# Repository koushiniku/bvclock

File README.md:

# bvclock
A wall clock on a breadboard.

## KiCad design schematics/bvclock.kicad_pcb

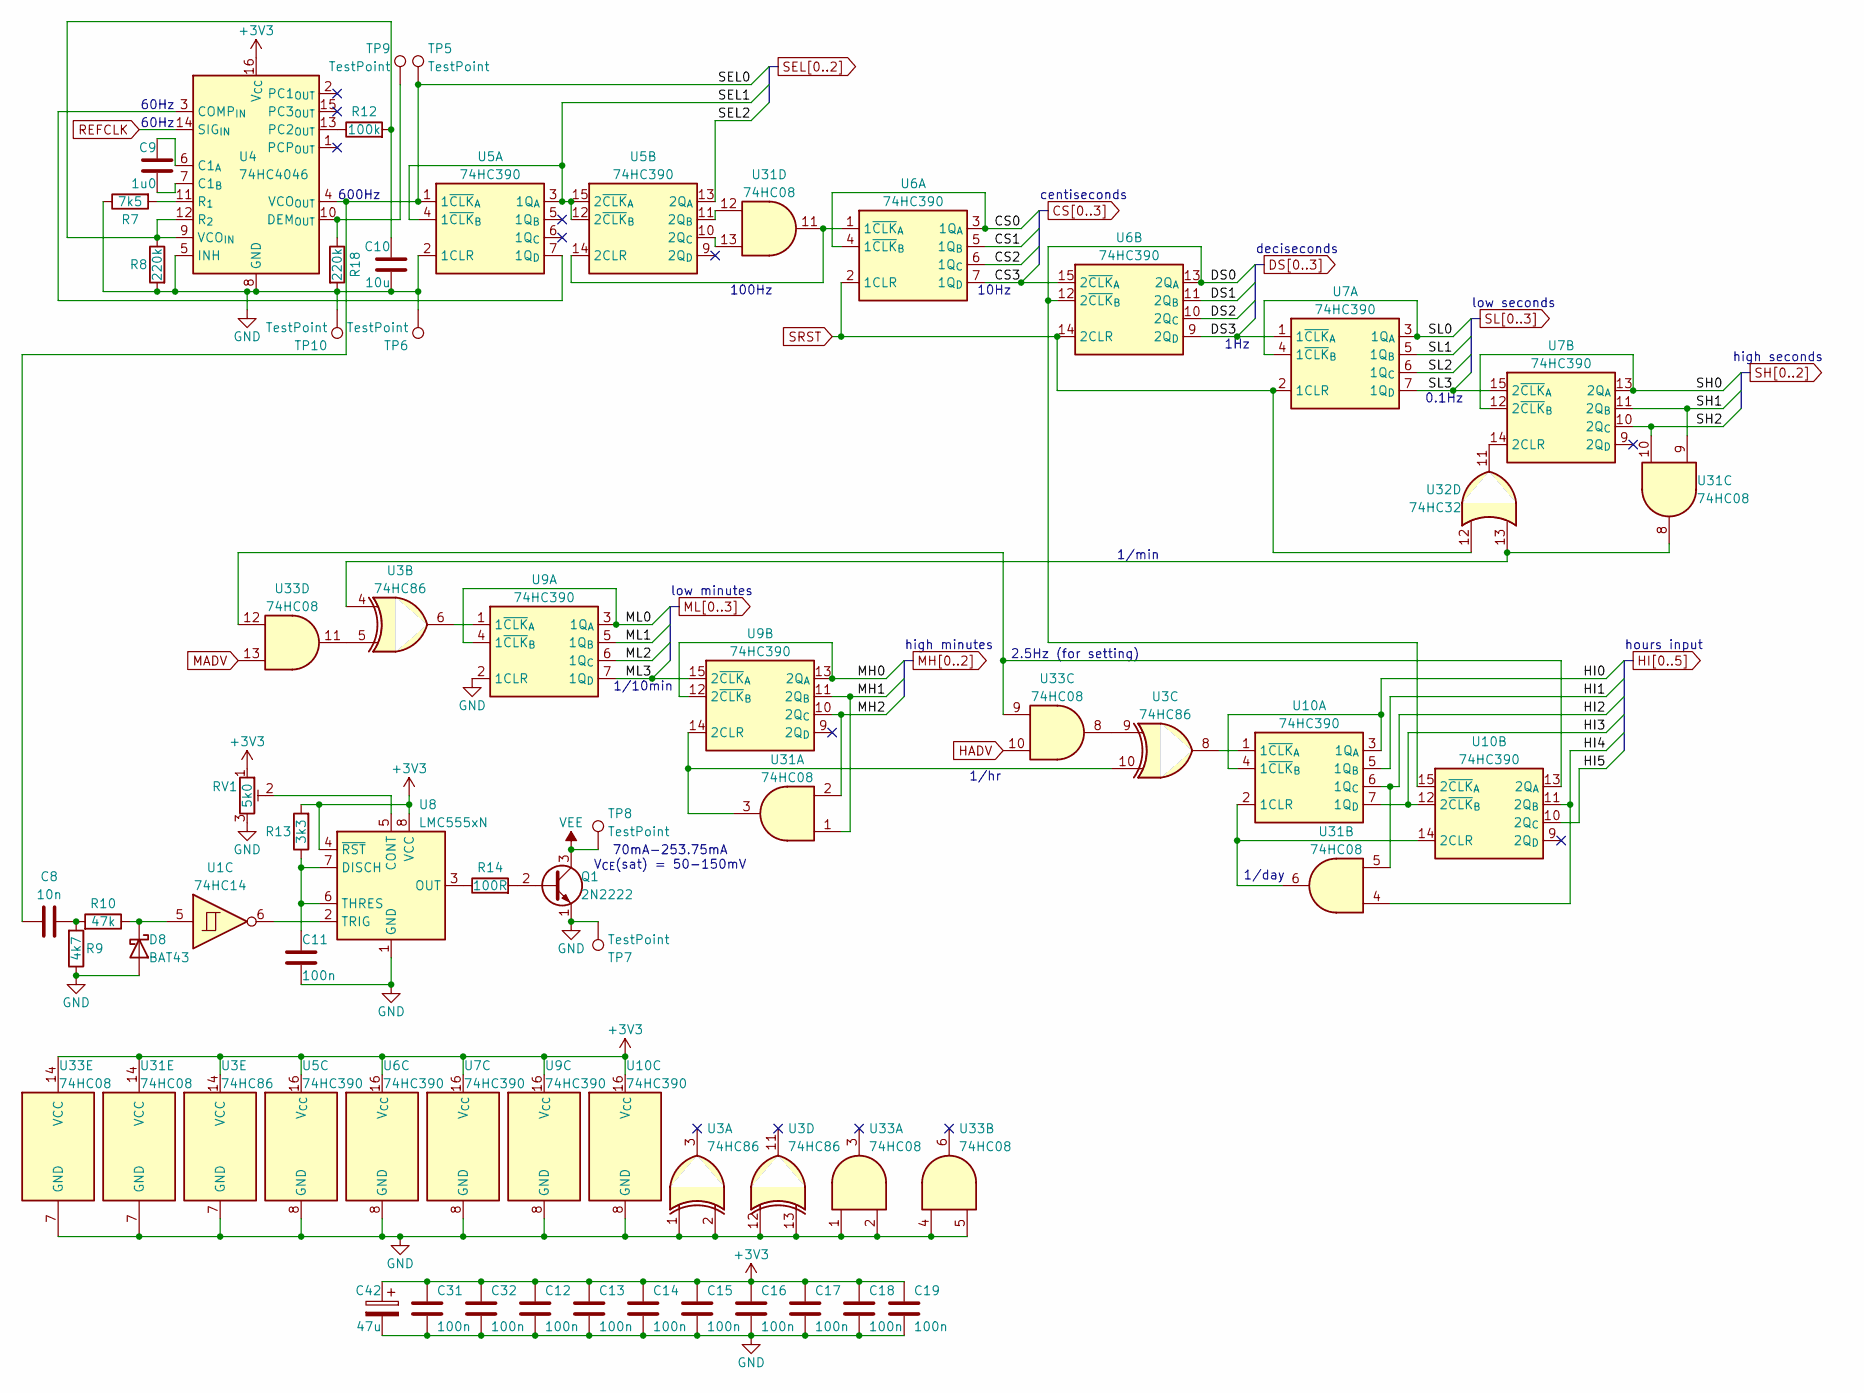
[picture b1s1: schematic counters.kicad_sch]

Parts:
C8: 10n; THT_Cap
C9: 1u0; THT_Cap
C10: 10u; THT_Cap
C11, C12, C13, C14, C15, C16, C17, C18, C19, C31, C32: 100n; THT_Cap
C42: 47u; CP_Radial_D5.0mm_P2.00mm
D8: BAT43; THT_D_Vertical
Q1: 2N2222; TO-92_HandSolder
R7: 7k5; THT_R_Vertical
R8, R18: 220k; THT_R_Vertical
R9: 4k7; THT_R_Vertical
R10: 47k; THT_R_Vertical
R12: 100k; THT_R_Vertical
R13: 3k3; THT_R_Vertical
R14: 100R; THT_R_Vertical
RV1: 5k0; Bourns_3362P_Trimming_Potentiometer
TP5, TP8, TP9: TestPoint; TestPoint_THTPad_2.5x2.5mm_Drill1.2mm
TP6, TP7, TP10: TestPoint; TestPoint_THTPad_D1.0mm_Drill0.5mm
U1: 74HC14; DIP-14_W7.62mm
U3: 74HC86; DIP-14_W7.62mm
U4: 74HC4046; DIP-16_W7.62mm
U5, U6, U7, U9, U10: 74HC390; DIP-16_W7.62mm
U8: LMC555xN; DIP-8_W7.62mm
U31, U33: 74HC08; DIP-14_W7.62mm
U32: 74HC32; DIP-14_W7.62mm

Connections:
+3V3: C12.1, C13.1, C14.1, C15.1, C16.1, C17.1, C18.1, C19.1, C31.1, C32.1, C42.1, R13.2, RV1.1, U3.14 (VCC), U4.16 (V_{CC}), U5.16 (V_{CC}), U6.16 (V_{CC}), U7.16 (V_{CC}), U8.4 (~RST), U8.8 (VCC), U9.16 (V_{CC}), U10.16 (V_{CC}), U31.14 (VCC), U33.14 (VCC); also elsewhere on the board
CS0: U6.3 (1Q_{A}), U6.4 (1~CLK_{B}); also elsewhere on the board
CS1: U6.5 (1Q_{B}); also elsewhere on the board
CS2: U6.6 (1Q_{C}); also elsewhere on the board
CS3: U6.7 (1Q_{D}), U6.15 (2~CLK_{A}); also elsewhere on the board
DS0: U6.12 (2~CLK_{B}), U6.13 (2Q_{A}), U10.15 (2~CLK_{A}); also elsewhere on the board
DS1: U6.11 (2Q_{B}); also elsewhere on the board
DS2: U6.10 (2Q_{C}); also elsewhere on the board
DS3: U6.9 (2Q_{D}), U7.1 (1~CLK_{A}); also elsewhere on the board
GND: C10.2, C11.2, C12.2, C13.2, C14.2, C15.2, C16.2, C17.2, C18.2, C19.2, C31.2, C32.2, C42.2, D8.2 (A), Q1.1 (E), R7.1, R8.2, R9.1, R18.2, RV1.3, TP6.1 (1_1), TP7.1 (1_1), TP10.1 (1_1), U3.1, U3.2, U3.7 (GND), U3.12, U3.13, U4.5 (INH), U4.8 (GND), U5.2 (1CLR), U5.8 (GND), U6.8 (GND), U7.8 (GND), U8.1 (GND), U9.2 (1CLR), U9.8 (GND), U10.8 (GND), U31.7 (GND), U33.1, U33.2, U33.4, U33.5, U33.7 (GND); also elsewhere on the board
HADV: U33.10; also elsewhere on the board
HI0: U10.3 (1Q_{A}), U10.4 (1~CLK_{B}); also elsewhere on the board
HI1: U10.5 (1Q_{B}); also elsewhere on the board
HI2: U10.6 (1Q_{C}), U31.5; also elsewhere on the board
HI3: U10.7 (1Q_{D}), U10.12 (2~CLK_{B}); also elsewhere on the board
HI4: U10.11 (2Q_{B}), U31.4; also elsewhere on the board
HI5: U10.10 (2Q_{C}); also elsewhere on the board
MADV: U33.13; also elsewhere on the board
MH0: U9.12 (2~CLK_{B}), U9.13 (2Q_{A}); also elsewhere on the board
MH1: U9.11 (2Q_{B}), U31.1; also elsewhere on the board
MH2: U9.10 (2Q_{C}), U31.2; also elsewhere on the board
ML0: U9.3 (1Q_{A}), U9.4 (1~CLK_{B}); also elsewhere on the board
ML1: U9.5 (1Q_{B}); also elsewhere on the board
ML2: U9.6 (1Q_{C}); also elsewhere on the board
ML3: U9.7 (1Q_{D}), U9.15 (2~CLK_{A}); also elsewhere on the board
unnamed: C8.2, R9.2, R10.2
unnamed: D8.1 (K), R10.1, U1.5
unnamed: Q1.2 (B), R14.2
unnamed: U3.4, U31.8, U32.13
unnamed: U3.5, U33.11
unnamed: U3.9, U33.8
unnamed: C9.1, U4.6 (C1_{A})
unnamed: C9.2, U4.7 (C1_{B})
unnamed: U4.3 (COMP_{IN}), U5.7 (1Q_{D})
unnamed: R18.1, TP9.1 (1_1), U4.10 (DEM_{OUT})
unnamed: R12.1, U4.13 (PC2_{OUT})
unnamed: R7.2, U4.11 (R_{1})
unnamed: C10.1, R8.1, R12.2, U4.9 (VCO_{IN}), U4.12 (R_{2})
unnamed: U5.14 (2CLR), U6.1 (1~CLK_{A}), U31.11
unnamed: U5.11 (2Q_{B}), U31.12
unnamed: U5.10 (2Q_{C}), U31.13
unnamed: U7.14 (2CLR), U32.11
unnamed: RV1.2, U8.5 (CONT)
unnamed: C11.1, R13.1, U8.6 (THRES), U8.7 (DISCH)
unnamed: R14.1, U8.3 (OUT)
unnamed: U1.6, U8.2 (TRIG)
unnamed: U3.6, U9.1 (1~CLK_{A})
unnamed: U3.10, U9.14 (2CLR), U31.3
unnamed: U10.2 (1CLR), U10.14 (2CLR), U31.6
unnamed: U3.8, U10.1 (1~CLK_{A})
unnamed: U10.13 (2Q_{A}), U33.9, U33.12
REFCLK: U4.14 (SIG_{IN}); also elsewhere on the board
SEL0: C8.1, TP5.1 (1_1), U4.4 (VCO_{OUT}), U5.1 (1~CLK_{A}); also elsewhere on the board
SEL1: U5.3 (1Q_{A}), U5.4 (1~CLK_{B}), U5.12 (2~CLK_{B}), U5.15 (2~CLK_{A}); also elsewhere on the board
SEL2: U5.13 (2Q_{A}); also elsewhere on the board
SH0: U7.12 (2~CLK_{B}), U7.13 (2Q_{A}); also elsewhere on the board
SH1: U7.11 (2Q_{B}), U31.9; also elsewhere on the board
SH2: U7.10 (2Q_{C}), U31.10; also elsewhere on the board
SL0: U7.3 (1Q_{A}), U7.4 (1~CLK_{B}); also elsewhere on the board
SL1: U7.5 (1Q_{B}); also elsewhere on the board
SL2: U7.6 (1Q_{C}); also elsewhere on the board
SL3: U7.7 (1Q_{D}), U7.15 (2~CLK_{A}); also elsewhere on the board
SRST: U6.2 (1CLR), U6.14 (2CLR), U7.2 (1CLR), U32.12; also elsewhere on the board
VEE: Q1.3 (C), TP8.1 (1_1); also elsewhere on the board

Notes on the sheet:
low minutes
1/day
hours input
60Hz
1/hr
0.1Hz
high seconds
2.5Hz (for setting)
high minutes
100Hz
70mA-253.75mA V_{CE}(sat) = 50-150mV
1/10min
low seconds
deciseconds
1Hz
600Hz
centiseconds
10Hz
1/min

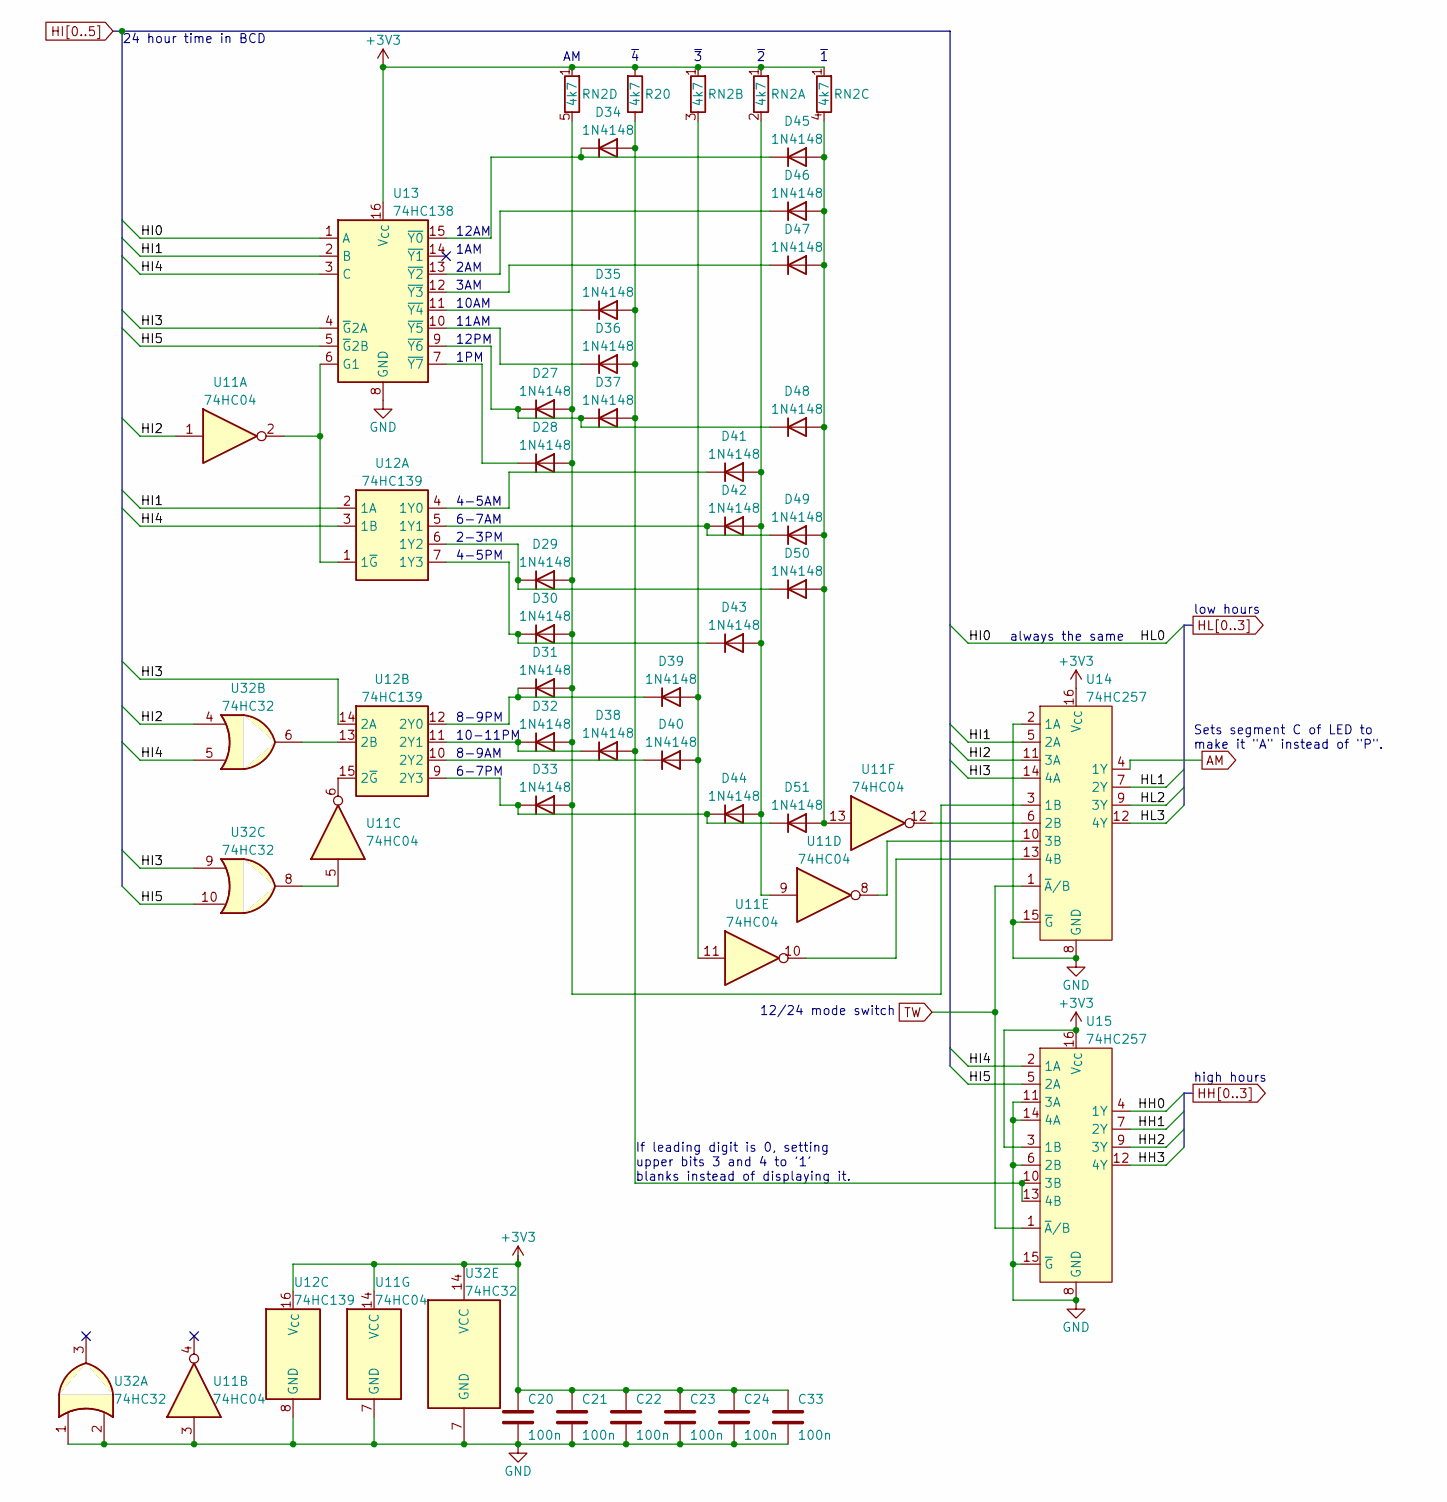
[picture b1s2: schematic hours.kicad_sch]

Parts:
C20, C21, C22, C23, C24, C33: 100n; THT_Cap
D27, D28, D29, D30, D31, D32, D33, D34, D35, D36, D37, D38, D39, D40, D41, D42, D43, D44, D45, D46, D47, D48, D49, D50, D51: 1N4148; THT_D_Vertical
R20: 4k7; THT_R_Vertical
RN2: 4k7; R_Array_SIP5
U11: 74HC04; DIP-14_W7.62mm
U12: 74HC139; DIP-16_W7.62mm
U13: 74HC138; DIP-16_W7.62mm
U14, U15: 74HC257; DIP-16_W7.62mm
U32: 74HC32; DIP-14_W7.62mm

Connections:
+3V3: C20.1, C21.1, C22.1, C23.1, C24.1, C33.1, R20.2, RN2.1 (R1), U11.14 (VCC), U12.16 (V_{CC}), U13.16 (V_{CC}), U14.16 (V_{CC}), U15.3 (1B), U15.16 (V_{CC}), U32.14 (VCC); also elsewhere on the board
AM: U14.4 (1Y); also elsewhere on the board
GND: C20.2, C21.2, C22.2, C23.2, C24.2, C33.2, U11.3, U11.7 (GND), U12.8 (GND), U13.8 (GND), U14.2 (1A), U14.8 (GND), U14.15 (~G), U15.6 (2B), U15.8 (GND), U15.11 (3A), U15.14 (4A), U15.15 (~G), U32.1, U32.2, U32.7 (GND); also elsewhere on the board
HH0: U15.4 (1Y); also elsewhere on the board
HH1: U15.7 (2Y); also elsewhere on the board
HH2: U15.9 (3Y); also elsewhere on the board
HH3: U15.12 (4Y); also elsewhere on the board
HI0: U13.1 (A); also elsewhere on the board
HI1: U12.2 (1A), U13.2 (B), U14.5 (2A); also elsewhere on the board
HI2: U11.1, U14.11 (3A), U32.4; also elsewhere on the board
HI3: U12.14 (2A), U13.4 (~G2A), U14.14 (4A), U32.9; also elsewhere on the board
HI4: U12.3 (1B), U13.3 (C), U15.2 (1A), U32.5; also elsewhere on the board
HI5: U13.5 (~G2B), U15.5 (2A), U32.10; also elsewhere on the board
HL1: U14.7 (2Y); also elsewhere on the board
HL2: U14.9 (3Y); also elsewhere on the board
HL3: U14.12 (4Y); also elsewhere on the board
unnamed: D27.2 (A), D28.2 (A), D29.2 (A), D30.2 (A), D31.2 (A), D32.2 (A), D33.2 (A), RN2.5 (R4.2), U14.3 (1B)
unnamed: D27.1 (K), D37.1 (K), D48.1 (K), U13.9 (~Y6)
unnamed: D28.1 (K), U13.7 (~Y7)
unnamed: D29.1 (K), D50.1 (K), U12.6 (1Y2)
unnamed: D30.1 (K), D43.1 (K), U12.7 (1Y3)
unnamed: D31.1 (K), D39.1 (K), U12.12 (2Y0)
unnamed: D32.1 (K), D38.1 (K), U12.11 (2Y1)
unnamed: D33.1 (K), D44.1 (K), D51.1 (K), U12.9 (2Y3)
unnamed: D34.2 (A), D35.2 (A), D36.2 (A), D37.2 (A), D38.2 (A), R20.1, U15.10 (3B), U15.13 (4B)
unnamed: D34.1 (K), D45.1 (K), U13.15 (~Y0)
unnamed: D35.1 (K), U13.11 (~Y4)
unnamed: D36.1 (K), U13.10 (~Y5)
unnamed: D39.2 (A), D40.2 (A), RN2.3 (R2.2), U11.11
unnamed: D40.1 (K), U12.10 (2Y2)
unnamed: D41.2 (A), D42.2 (A), D43.2 (A), D44.2 (A), RN2.2 (R1.2), U11.9
unnamed: D41.1 (K), U12.4 (1Y0)
unnamed: D42.1 (K), D49.1 (K), U12.5 (1Y1)
unnamed: D45.2 (A), D46.2 (A), D47.2 (A), D48.2 (A), D49.2 (A), D50.2 (A), D51.2 (A), RN2.4 (R3.2), U11.13
unnamed: D46.1 (K), U13.13 (~Y2)
unnamed: D47.1 (K), U13.12 (~Y3)
unnamed: U11.5, U32.8
unnamed: U11.2, U12.1 (1~G), U13.6 (G1)
unnamed: U12.13 (2B), U32.6
unnamed: U11.6, U12.15 (2~G)
unnamed: U11.12, U14.6 (2B)
unnamed: U11.8, U14.10 (3B)
unnamed: U11.10, U14.13 (4B)
TW: U14.1 (~A/B), U15.1 (~A/B); also elsewhere on the board

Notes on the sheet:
If leading digit is 0, setting upper bits 3 and 4 to '1' blanks instead of displaying it.
4-5AM
2AM
24 hour time in BCD
~{3}
~{2}
12AM
1AM
12/24 mode switch
low hours
11AM
6-7PM
6-7AM
2-3PM
1PM
12PM
Sets segment C of LED to make it "A" instead of "P".
3AM
10AM
high hours
~{4}
~{1}
8-9PM
always the same
8-9AM
4-5PM
10-11PM

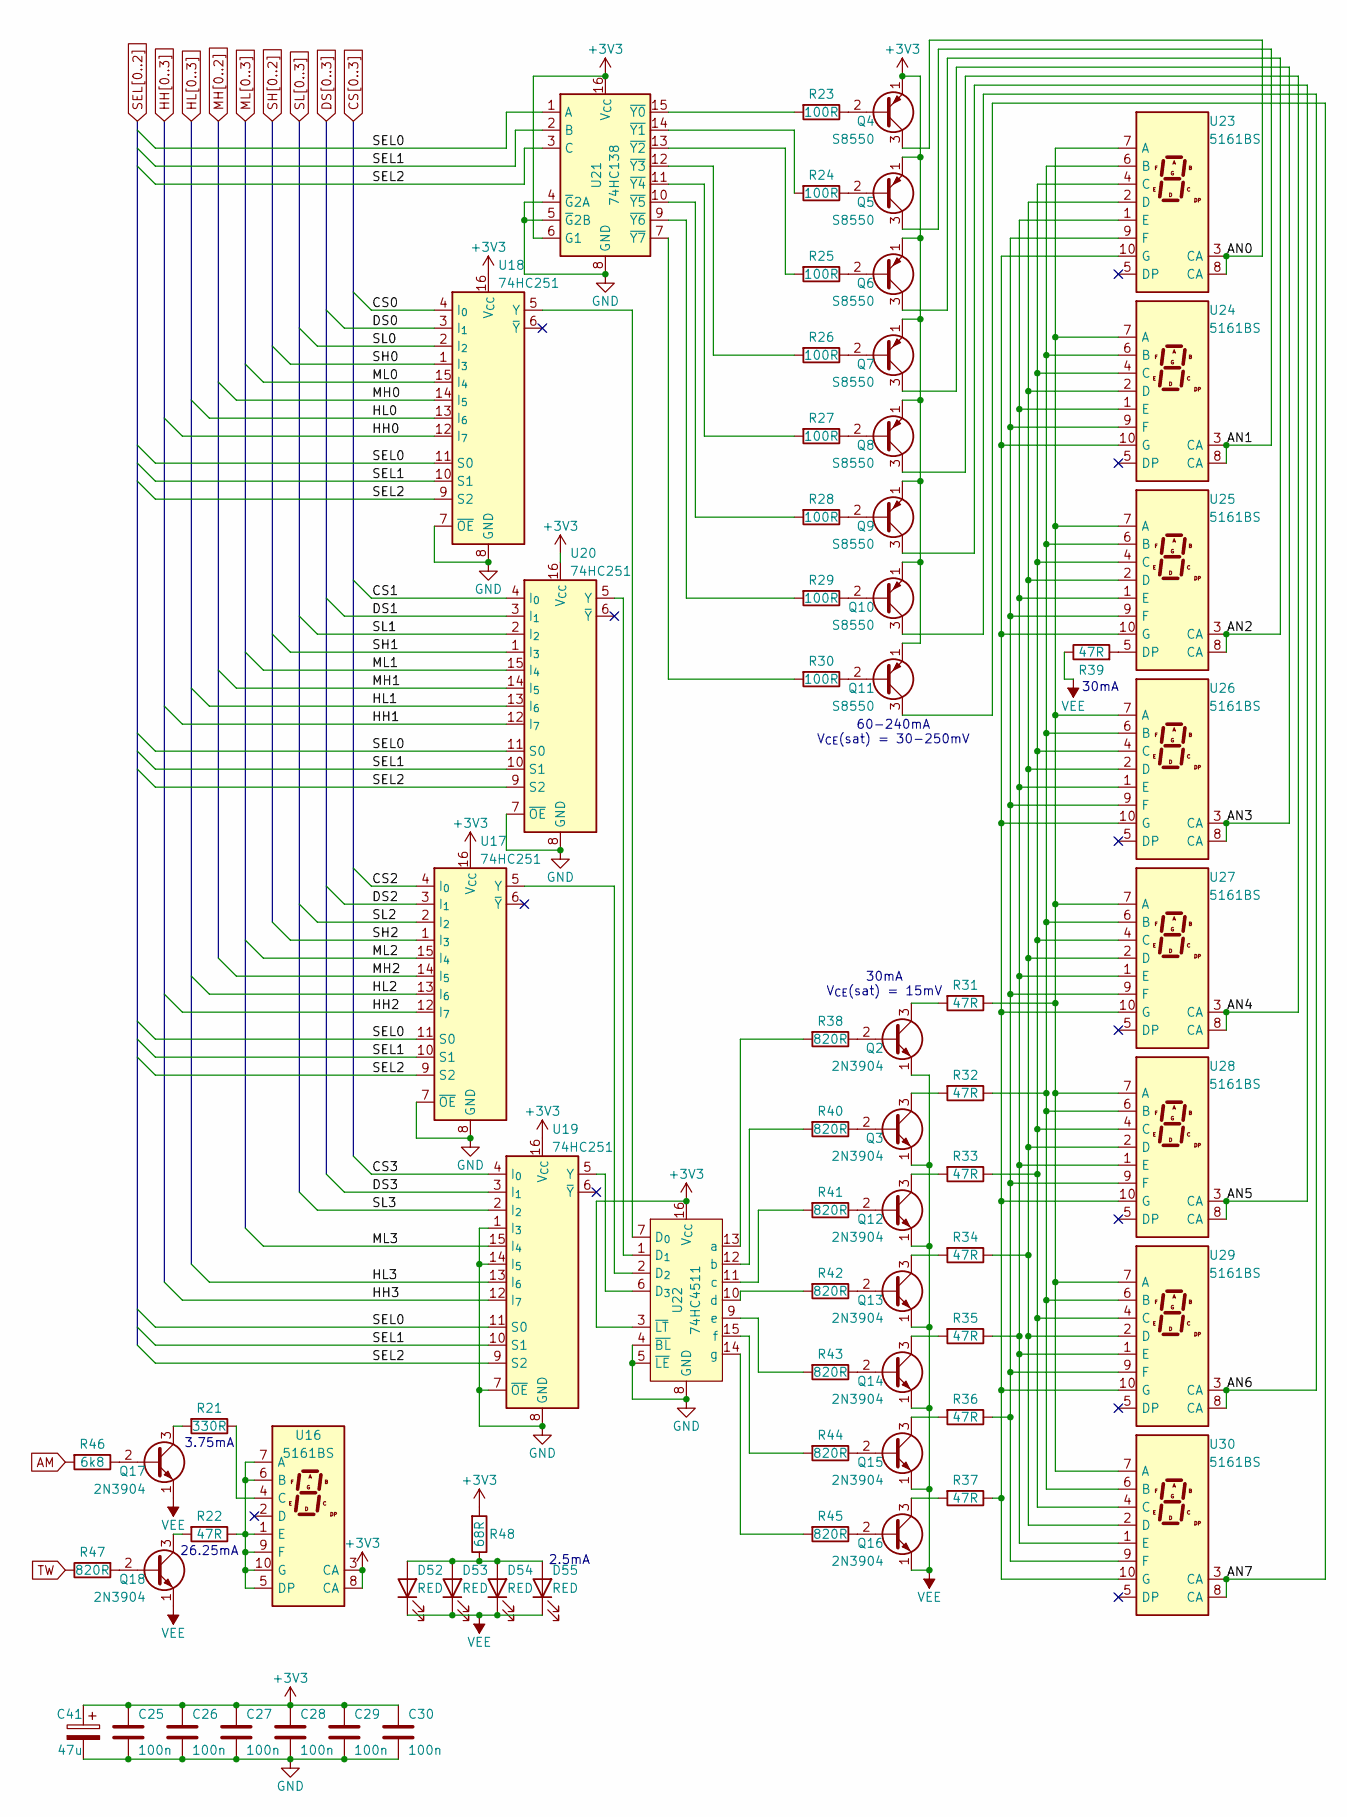
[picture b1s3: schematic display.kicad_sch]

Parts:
C25, C26, C27, C28, C29, C30: 100n; THT_Cap
C41: 47u; CP_Radial_D5.0mm_P2.00mm
D52, D53, D54, D55: RED; LED_D5.0mm
Q2, Q3, Q12, Q13, Q14, Q15, Q16, Q17, Q18: 2N3904; TO-92_HandSolder
Q4, Q5, Q6, Q7, Q8, Q9, Q10, Q11: S8550; TO-92_HandSolder
R21: 330R; THT_R_Vertical
R22, R31, R32, R33, R34, R35, R36, R37, R39: 47R; THT_R_Vertical
R23, R24, R25, R26, R27, R28, R29, R30: 100R; THT_R_Vertical
R38, R40, R41, R42, R43, R44, R45, R47: 820R; THT_R_Vertical
R46: 6k8; THT_R_Vertical
R48: 68R; THT_R_Vertical
U16, U23, U24, U25, U26, U27, U28, U29, U30: 5161BS; 7SegmentLED_LTS6760_LTS6780
U17, U18, U19, U20: 74HC251; DIP-16_W7.62mm
U21: 74HC138; DIP-16_W7.62mm
U22: 74HC4511; DIP-16_W7.62mm

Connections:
+3V3: C25.1, C26.1, C27.1, C28.1, C29.1, C30.1, C41.1, Q4.1 (E), Q5.1 (E), Q6.1 (E), Q7.1 (E), Q8.1 (E), Q9.1 (E), Q10.1 (E), Q11.1 (E), R48.2, U16.3 (CA), U16.8 (CA), U17.16 (V_{CC}), U18.16 (V_{CC}), U19.16 (V_{CC}), U20.16 (V_{CC}), U21.6 (G1), U21.16 (V_{CC}), U22.3 (~LT), U22.16 (V_{CC}); also elsewhere on the board
/display/AN0: Q4.3 (C), U23.3 (CA), U23.8 (CA)
/display/AN1: Q5.3 (C), U24.3 (CA), U24.8 (CA)
/display/AN2: Q6.3 (C), U25.3 (CA), U25.8 (CA)
/display/AN3: Q7.3 (C), U26.3 (CA), U26.8 (CA)
/display/AN4: Q8.3 (C), U27.3 (CA), U27.8 (CA)
/display/AN5: Q9.3 (C), U28.3 (CA), U28.8 (CA)
/display/AN6: Q10.3 (C), U29.3 (CA), U29.8 (CA)
/display/AN7: Q11.3 (C), U30.3 (CA), U30.8 (CA)
AM: R46.2; also elsewhere on the board
CS0: U18.4 (I_{0}); also elsewhere on the board
CS1: U20.4 (I_{0}); also elsewhere on the board
CS2: U17.4 (I_{0}); also elsewhere on the board
CS3: U19.4 (I_{0}); also elsewhere on the board
DS0: U18.3 (I_{1}); also elsewhere on the board
DS1: U20.3 (I_{1}); also elsewhere on the board
DS2: U17.3 (I_{1}); also elsewhere on the board
DS3: U19.3 (I_{1}); also elsewhere on the board
GND: C25.2, C26.2, C27.2, C28.2, C29.2, C30.2, C41.2, U17.7 (~OE), U17.8 (GND), U18.7 (~OE), U18.8 (GND), U19.1 (I_{3}), U19.7 (~OE), U19.8 (GND), U19.14 (I_{5}), U20.7 (~OE), U20.8 (GND), U21.4 (~G2A), U21.5 (~G2B), U21.8 (GND), U22.4 (~BL), U22.5 (~LE), U22.8 (GND); also elsewhere on the board
HH0: U18.12 (I_{7}); also elsewhere on the board
HH1: U20.12 (I_{7}); also elsewhere on the board
HH2: U17.12 (I_{7}); also elsewhere on the board
HH3: U19.12 (I_{7}); also elsewhere on the board
HI0: U18.13 (I_{6}); also elsewhere on the board
HL1: U20.13 (I_{6}); also elsewhere on the board
HL2: U17.13 (I_{6}); also elsewhere on the board
HL3: U19.13 (I_{6}); also elsewhere on the board
MH0: U18.14 (I_{5}); also elsewhere on the board
MH1: U20.14 (I_{5}); also elsewhere on the board
MH2: U17.14 (I_{5}); also elsewhere on the board
ML0: U18.15 (I_{4}); also elsewhere on the board
ML1: U20.15 (I_{4}); also elsewhere on the board
ML2: U17.15 (I_{4}); also elsewhere on the board
ML3: U19.15 (I_{4}); also elsewhere on the board
unnamed: D52.2 (A), D53.2 (A), D54.2 (A), D55.2 (A), R48.1
unnamed: Q2.2 (B), R38.1
unnamed: Q2.3 (C), R31.2
unnamed: Q3.2 (B), R40.1
unnamed: Q3.3 (C), R32.2
unnamed: Q4.2 (B), R23.1
unnamed: Q5.2 (B), R24.1
unnamed: Q6.2 (B), R25.1
unnamed: Q7.2 (B), R26.1
unnamed: Q8.2 (B), R27.1
unnamed: Q9.2 (B), R28.1
unnamed: Q10.2 (B), R29.1
unnamed: Q11.2 (B), R30.1
unnamed: Q12.2 (B), R41.1
unnamed: Q12.3 (C), R33.2
unnamed: Q13.2 (B), R42.1
unnamed: Q13.3 (C), R34.2
unnamed: Q14.2 (B), R43.1
unnamed: Q14.3 (C), R35.2
unnamed: Q15.2 (B), R44.1
unnamed: Q15.3 (C), R36.2
unnamed: Q16.2 (B), R45.1
unnamed: Q16.3 (C), R37.2
unnamed: Q17.2 (B), R46.1
unnamed: Q17.3 (C), R21.2
unnamed: Q18.2 (B), R47.2
unnamed: Q18.3 (C), R22.2
unnamed: R22.1, U16.1 (E), U16.5 (DP), U16.6 (B), U16.7 (A), U16.9 (F), U16.10 (G)
unnamed: R21.1, U16.4 (C)
unnamed: U17.5 (Y), U22.2 (D_{2})
unnamed: U18.5 (Y), U22.7 (D_{0})
unnamed: U19.5 (Y), U22.6 (D_{3})
unnamed: U20.5 (Y), U22.1 (D_{1})
unnamed: R23.2, U21.15 (~Y0)
unnamed: R24.2, U21.14 (~Y1)
unnamed: R25.2, U21.13 (~Y2)
unnamed: R26.2, U21.12 (~Y3)
unnamed: R27.2, U21.11 (~Y4)
unnamed: R28.2, U21.10 (~Y5)
unnamed: R29.2, U21.9 (~Y6)
unnamed: R30.2, U21.7 (~Y7)
unnamed: R38.2, U22.13 (a)
unnamed: R40.2, U22.12 (b)
unnamed: R41.2, U22.11 (c)
unnamed: R42.2, U22.10 (d)
unnamed: R43.2, U22.9 (e)
unnamed: R44.2, U22.15 (f)
unnamed: R45.2, U22.14 (g)
unnamed: R31.1, U23.7 (A), U24.7 (A), U25.7 (A), U26.7 (A), U27.7 (A), U28.7 (A), U29.7 (A), U30.7 (A)
unnamed: R32.1, U23.6 (B), U24.6 (B), U25.6 (B), U26.6 (B), U27.6 (B), U28.6 (B), U29.6 (B), U30.6 (B)
unnamed: R33.1, U23.4 (C), U24.4 (C), U25.4 (C), U26.4 (C), U27.4 (C), U28.4 (C), U29.4 (C), U30.4 (C)
unnamed: R34.1, U23.2 (D), U24.2 (D), U25.2 (D), U26.2 (D), U27.2 (D), U28.2 (D), U29.2 (D), U30.2 (D)
unnamed: R35.1, U23.1 (E), U24.1 (E), U25.1 (E), U26.1 (E), U27.1 (E), U28.1 (E), U29.1 (E), U30.1 (E)
unnamed: R36.1, U23.9 (F), U24.9 (F), U25.9 (F), U26.9 (F), U27.9 (F), U28.9 (F), U29.9 (F), U30.9 (F)
unnamed: R37.1, U23.10 (G), U24.10 (G), U25.10 (G), U26.10 (G), U27.10 (G), U28.10 (G), U29.10 (G), U30.10 (G)
unnamed: R39.2, U25.5 (DP)
SEL0: U17.11 (S0), U18.11 (S0), U19.11 (S0), U20.11 (S0), U21.1 (A); also elsewhere on the board
SEL1: U17.10 (S1), U18.10 (S1), U19.10 (S1), U20.10 (S1), U21.2 (B); also elsewhere on the board
SEL2: U17.9 (S2), U18.9 (S2), U19.9 (S2), U20.9 (S2), U21.3 (C); also elsewhere on the board
SH0: U18.1 (I_{3}); also elsewhere on the board
SH1: U20.1 (I_{3}); also elsewhere on the board
SH2: U17.1 (I_{3}); also elsewhere on the board
SL0: U18.2 (I_{2}); also elsewhere on the board
SL1: U20.2 (I_{2}); also elsewhere on the board
SL2: U17.2 (I_{2}); also elsewhere on the board
SL3: U19.2 (I_{2}); also elsewhere on the board
TW: R47.1; also elsewhere on the board
VEE: D52.1 (K), D53.1 (K), D54.1 (K), D55.1 (K), Q2.1 (E), Q3.1 (E), Q12.1 (E), Q13.1 (E), Q14.1 (E), Q15.1 (E), Q16.1 (E), Q17.1 (E), Q18.1 (E), R39.1; also elsewhere on the board

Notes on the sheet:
60-240mA V_{CE}(sat) = 30-250mV
30mA
26.25mA
30mA V_{CE}(sat) = 15mV
3.75mA
2.5mA

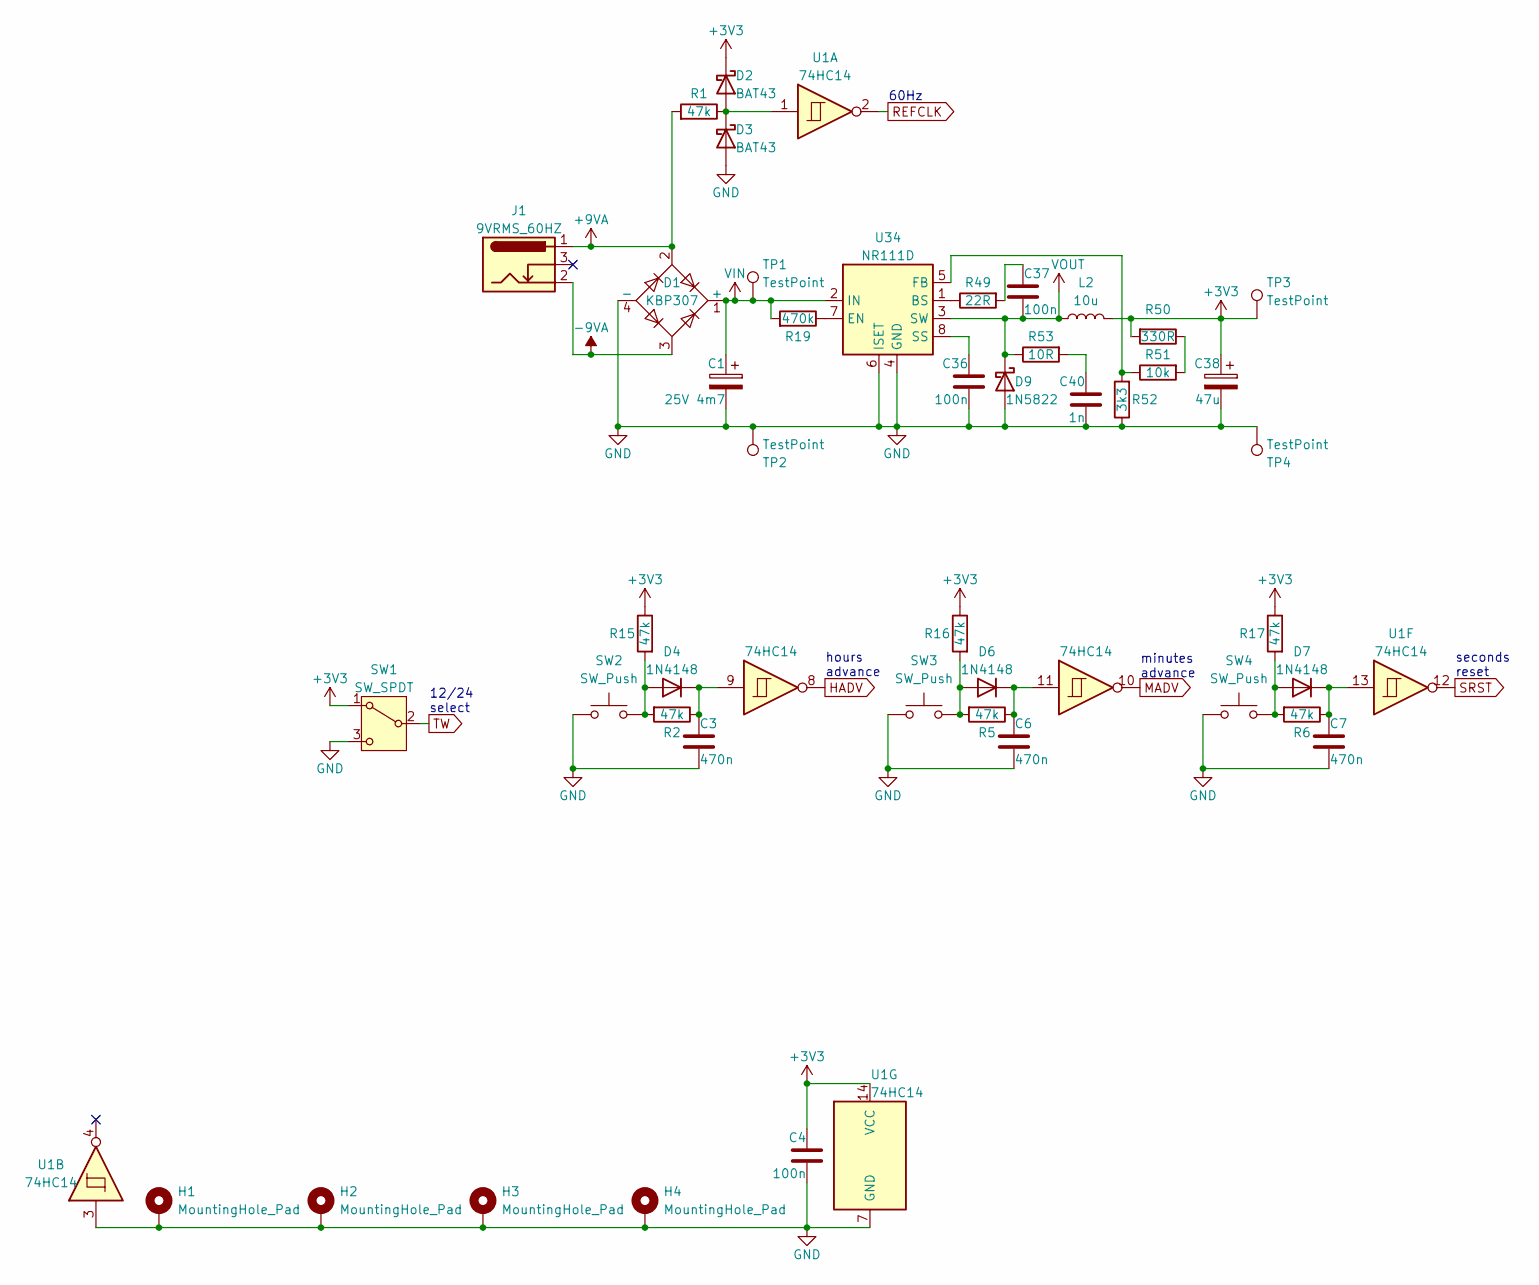
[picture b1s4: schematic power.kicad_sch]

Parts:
C1: 25V 4m7; CP_Radial_D16.0mm_P7.50mm
C3, C6, C7: 470n; THT_Cap
C4, C36, C37: 100n; THT_Cap
C38: 47u; CP_Radial_D5.0mm_P2.00mm
C40: 1n; THT_Cap
D1: KBP307; Diode_Bridge_Vishay_KBPM
D2, D3: BAT43; THT_D_Vertical
D4, D6, D7: 1N4148; THT_D_Vertical
D9: 1N5822; D_DO-201AD_P15.24mm_Horizontal
H1, H2, H3, H4: MountingHole_Pad; MountingHole_2.2mm_M2_ISO7380_Pad_TopBottom
J1: 9VRMS_60HZ; BarrelJack_Horizontal
L2: 10u; L_Toroid_Vertical_L14.9mm_W8.0mm_P7.40mm
R1, R2, R5, R6, R15, R16, R17: 47k; THT_R_Vertical
R19: 470k; THT_R_Vertical
R49: 22R; THT_R_Vertical
R50: 330R; THT_R_Vertical
R51: 10k; THT_R_Vertical
R52: 3k3; THT_R_Vertical
R53: 10R; THT_R_Vertical
SW1: SW_SPDT; SW_Slide_SPDT
SW2, SW3, SW4: SW_Push
TP1, TP3: TestPoint; TestPoint_THTPad_2.5x2.5mm_Drill1.2mm
TP2, TP4: TestPoint; TestPoint_THTPad_D1.0mm_Drill0.5mm
U1: 74HC14; DIP-14_W7.62mm
U34: NR111D; DIP-8_W7.62mm

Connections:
+3V3: C4.1, C38.1, D2.1 (K), L2.2, R15.1, R16.1, R17.1, R50.2, SW1.1 (A), TP3.1 (1_1), U1.14 (VCC); also elsewhere on the board
+9VA: D1.2, J1.1, R1.2
-9VA: D1.3, J1.2
GND: C1.2, C3.2, C4.2, C6.2, C7.2, C36.2, C38.2, C40.2, D1.4 (-), D3.2 (A), D9.2 (A), H1.1 (1_1), H2.1 (1_1), H3.1 (1_1), H4.1 (1_1), R52.1, SW1.3 (C), SW2.1, SW3.1, SW4.1, TP2.1 (1_1), TP4.1 (1_1), U1.3, U1.7 (GND), U34.4 (GND), U34.6 (ISET); also elsewhere on the board
HADV: U1.8; also elsewhere on the board
MADV: U1.10; also elsewhere on the board
unnamed: C37.1, R49.2
unnamed: C40.1, R53.2
unnamed: D2.2 (A), D3.1 (K), R1.1, U1.1
unnamed: D4.2 (A), R2.2, R15.2, SW2.2
unnamed: C3.1, D4.1 (K), R2.1, U1.9
unnamed: D6.2 (A), R5.2, R16.2, SW3.2
unnamed: C6.1, D6.1 (K), R5.1, U1.11
unnamed: D7.2 (A), R6.2, R17.2, SW4.2
unnamed: C7.1, D7.1 (K), R6.1, U1.13
unnamed: R50.1, R51.2
unnamed: R49.1, U34.1 (BS)
unnamed: R19.1, U34.7 (EN)
unnamed: R51.1, R52.2, U34.5 (FB)
unnamed: C36.1, U34.8 (SS)
REFCLK: U1.2; also elsewhere on the board
SRST: U1.12; also elsewhere on the board
TW: SW1.2 (B); also elsewhere on the board
VIN: C1.1, D1.1 (+), R19.2, TP1.1 (1_1), U34.2 (IN)
VOUT: C37.2, D9.1 (K), L2.1, R53.1, U34.3 (SW)

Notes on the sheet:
seconds reset
hours advance
60Hz
minutes advance
12/24 select

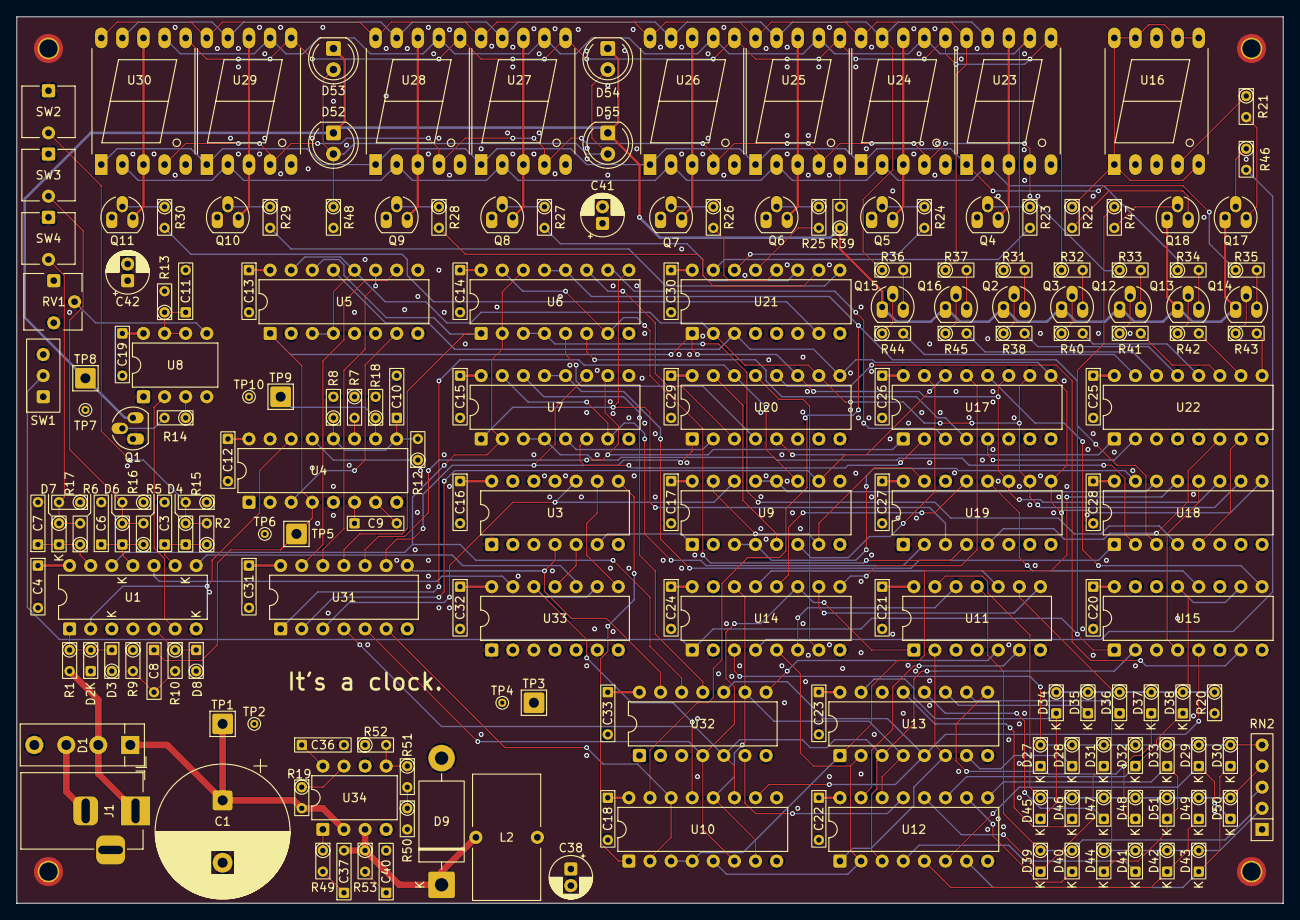
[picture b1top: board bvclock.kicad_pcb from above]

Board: 4 copper layers, 152.4 x 106.7 mm, 197 parts (0 on the bottom side), 182 nets.
